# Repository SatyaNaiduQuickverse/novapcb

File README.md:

# novapcb — Nova Flight Controller (FC) PCB

Custom flight controller board for the Nova drone platform. **Status: scoping / greenfield.** No schematics committed yet.

## What this is

A from-scratch FC PCB that drops into the existing Nova drone-Pi software stack. It must remain wire-compatible with the autopilot the system currently uses (a Holybro Pixhawk 6X over USB-CDC MAVLink), because the rest of the stack — ELRS RC link, MAVROS, BLE pre-flight, Hailo vision, phone app — all assumes that contract and is already integrated end-to-end. v1 = functional drop-in, single-PCB on a new tray. v2 = FMUv6X mechanical drop-in.

This is not an attempt to write a new autopilot. The plan is to run an ArduPilot-compatible firmware (or MAVLink-shim equivalent) on a custom board sized and connectorized to fit the Nova frame, with sensors and IO chosen for our specific airframe.

## What this is NOT

- Not the drone-side Pi services. Those live in `~/drone_handoff` (CRSF translator, MAVROS telemetry pump, BLE GATT server) — see `docs/SYSTEM_CONTEXT.md`.
- Not the ground bridge or phone app. Those are `~/novaros` and `~/novaapp_recovery`.
- Not a from-scratch flight stack. The board must speak ArduPilot/MAVLink.

## Repo layout

```
hardware/
  kicad/        # schematic + PCB sources (KiCad 8)
  exports/      # gerbers, drill, pick-and-place — generated, not handwritten
docs/
  SYSTEM_CONTEXT.md       # where the FC sits in the Nova stack
  INTERFACE_CONTRACT.md   # exact pin / protocol contract with the rest of the system
  DECISIONS.md            # locked v1 scoping decisions (MCU, form factor, channels, …)
  OPEN_QUESTIONS.md       # stub for future open questions (post-2026-05-18 lock)
firmware/      # ArduPilot board definition + any board-bringup code
bom/           # parts list, sourcing notes
mechanical/    # mounting holes, stack-up, frame-fit references
```

## Where to start reading

1. `docs/SYSTEM_CONTEXT.md` — the wider Nova stack the FC plugs into.
2. `docs/INTERFACE_CONTRACT.md` — pin-level constraints.
3. `docs/DESIGN_PHASES.md` — canonical execution plan (Phase 0..9 + 0.5/2.5/3.5/6.5).
4. `docs/CONFIDENCE_MAP.md` — subsystem confidence + evidence.
5. `docs/ENGINEERING_RIGOR.md` — non-negotiable commitments.
6. `docs/SIMULATION_PLAN.md` — Phase 6 sim detail.
7. `docs/TASK_CONTRACTS.md` — input/output contracts per sub-phase.
8. `docs/RETROSPECTIVES.md` — hourly self-review framework.
9. `docs/COORDINATION.md` — supervisor + nova-coord setup.
10. `docs/COMMUNICATION.md` — master ↔ worker protocol.
11. `docs/DECISIONS.md` — locked v1 scoping decisions.

## Workflow

PCB work on this project is code-driven where it can be: sources in KiCad, exports automated, BOM diffable. The intent is to keep schematic/layout reviewable in PRs the same way firmware changes are. See `CLAUDE.md` §6 for the full workflow.

## Hardware host

Design and build environment is a Raspberry Pi 5 (16 GB) with a Hailo-8 hat — the same Pi that runs the drone-side stack in dockerized form. KiCad runs natively on the Pi.

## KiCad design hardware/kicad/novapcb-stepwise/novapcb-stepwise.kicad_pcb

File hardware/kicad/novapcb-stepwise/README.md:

# novapcb-stepwise — incremental-integration board (v1.1+)

The single `.kicad_pcb` that grows subsystem by subsystem per
`docs/PLACEMENT_ROUTING_GATES.md` §0 and the integration order in
`docs/SUBSYSTEM_CONTRACTS.md` §4.

## Status

- **Step 1 (C — MCU_CORE):** placed + gates 1/3/4/12 GREEN.
- **Step 2 (E — BARO_I2C):** placed (U4, U7, C51, C52, C71, C72, R11, R12).
- Steps 3-10: future PRs (one per subsystem / integration step).

## How to regenerate

```bash
# Step 1 — place C only
python3 step1_place_C.py
# Step 2 — add E (BARO_I2C) on top of the Step-1 board
python3 step2_place_E.py

# Run the gates (each returns 0 = green, 1 = fail)
python3 gate1_bbox_overlap.py    # bbox-overlap + self-test
python3 gate3_uniqueness.py      # netlist ↔ pcb match
python3 gate4_artifact_trust.py  # grep-the-artifact audit
python3 gate12_thermal_U1.py     # per-subsystem thermal (U1 T_j)

# Gate 2 — 3D render (visual eyeball for master audit)
kicad-cli pcb render --side top    --output render_top.png novapcb-stepwise.kicad_pcb
kicad-cli pcb render --side bottom --output render_bot.png novapcb-stepwise.kicad_pcb
```

## Files

| File | Purpose |
|---|---|
| `novapcb-stepwise.kicad_pcb` | the growing board (committed) |
| `fp-lib-table`               | absolute-path footprint libs (KiCad 9 KIPRJMOD workaround) |
| `step1_place_C.py`           | Step-1 placer: U1, Y1, FB1, 16 caps, 3 resistors |
| `step2_place_E.py`           | Step-2 placer: U4 (DPS310), U7 (BMP388), C51/52/71/72, R11/12 |
| `gate1_bbox_overlap.py`      | Gate 1 verifier (with deliberate-bad self-test) |
| `gate3_uniqueness.py`        | Gate 3: every netlist refdes in .kicad_pcb exactly once |
| `gate4_artifact_trust.py`    | Gate 4: parse the actual .kicad_pcb, don't trust placer's "OK" |
| `gate12_thermal_U1.py`       | Gate 12: U1 worst-case T_j (analytical + Elmer FE attempt) |
| `render_top.png` / `render_bot.png` | Gate 2: 3D renders (visual audit) |

## Step 1 — C (MCU_CORE) placement summary

Per `docs/SUBSYSTEM_CONTRACTS.md §C`:

- **U1** STM32H743VIT6 LQFP-100 at **(45, 35)** mm — geometric center of board.
- **Y1** 8 MHz HSE crystal at W edge, vertically between U1 pins 12 (PH0)
  and 13 (PH1). Rotated 90° so the 3.2 mm dim is in Y.
- **C24, C25** xtal load caps (18 pF) flanking Y1, further W.
- **C11..C15** per-VDD-pin 100 nF decap (5 caps, one per VDD pin: 11 W, 27 S,
  50 S, 75 E, 100 N).
- **C17** (VCAP1, 2.2 µF) S band near pin 48.
- **C18** (VCAP2, 2.2 µF) E band near pin 73.
- **C19, C20, FB1** VDDA chain (100 nF + 1 µF + ferrite) W band near pin 21.
- **C21, C22, R1** VREF+ chain (100 nF + 1 µF + 0R tie) W band near pin 20.
- **C23, R2** VBAT (100 nF + 0R tie to +3V3) W band near pin 6.
- **C26** NRST decap (100 nF) W band near pin 14.
- **R3** BOOT0 pulldown (10k) N band near pin 94.
- **C16** bulk decoupling (4.7 µF 0805) N band, +X-offset from R3.

All 22 C-subsystem footprints + U1 + 4 corner mounting holes are on-board.
The remaining 103 footprints (subsystems A, B, D, E, F, G, H) are PARKED at
X ≥ 110 mm — they will be positioned by future Step-N PRs.

## Sub-phase 1.0 — workflow workaround

KiCad 9's `pcbnew.FootprintLoad` returns `None` for `kinet2pcb`, so we
**clone-and-strip** the v1.1 source `.kicad_pcb` (which has all 125
SKiDL-generated footprints already loaded) via an S-expression rewrite
that drops tracks/vias/zones/Edge.Cuts shapes/original mounting holes.
`pcbnew` then handles repositioning. See `step1_place_C.py:sexp_strip()`.

## Gate-7 note

LQFP-100 (`Package_QFP:LQFP-100_14x14mm_P0.5mm`) is a gull-wing
package — **no exposed thermal pad** — so Gate 7 thermal-vias-under-U1
is N/A. The MCU dissipates ≤500 mW through its 100 leads to the planes
(planes added in the cross-subsystem routing PR).

## Gate-12 note

Two-track T_j evidence per `docs/PLACEMENT_ROUTING_GATES.md` §Gate 13:

- **Analytical (with planes, JESD51-7):** T_j worst = 47.5 °C at P=0.5W,
  T_amb=25°C, Theta_ja=45°C/W (ST DS12110 §6.1). Margin to 105°C
  spec = **57.5 °C**. The cross-subsystem +3V3 + GND planes (added in
  the cross-subsystem routing PR) deliver this regime.
- **Elmer 3D FE (bare FR4, no planes):** T_j ≈ 103 °C. **Marginal**
  (1.8°C from spec) but expected — bare FR4 has no copper spreader,
  so this is a worst-case lower bound for the placement before planes
  land. As soon as the +3V3 / GND planes are present, T_j drops toward
  the analytical 47.5°C.

**3D body-source convention lesson (caught 2026-05-22):** Elmer's
`HeatSolver` expects `Heat Source` in **W/kg** (per unit MASS), not
W/m³. Solver internally multiplies by `Density`. Setting raw W/m³
over-sources by the density factor (~1850× for FR4). Validated against
1D thin-slab analytical to **1.00× match** — see
`sims/validation/VALIDATION_RESULTS.md` §3.

Convergence note: medium→fine mesh delta is 5.63% (just above the <5%
bar). The next iteration of `gate12_thermal_U1.py` should push to a
finer mesh or document why 5.6% is acceptable for a "bare-FR4
upper bound that won't be the ship-state anyway."

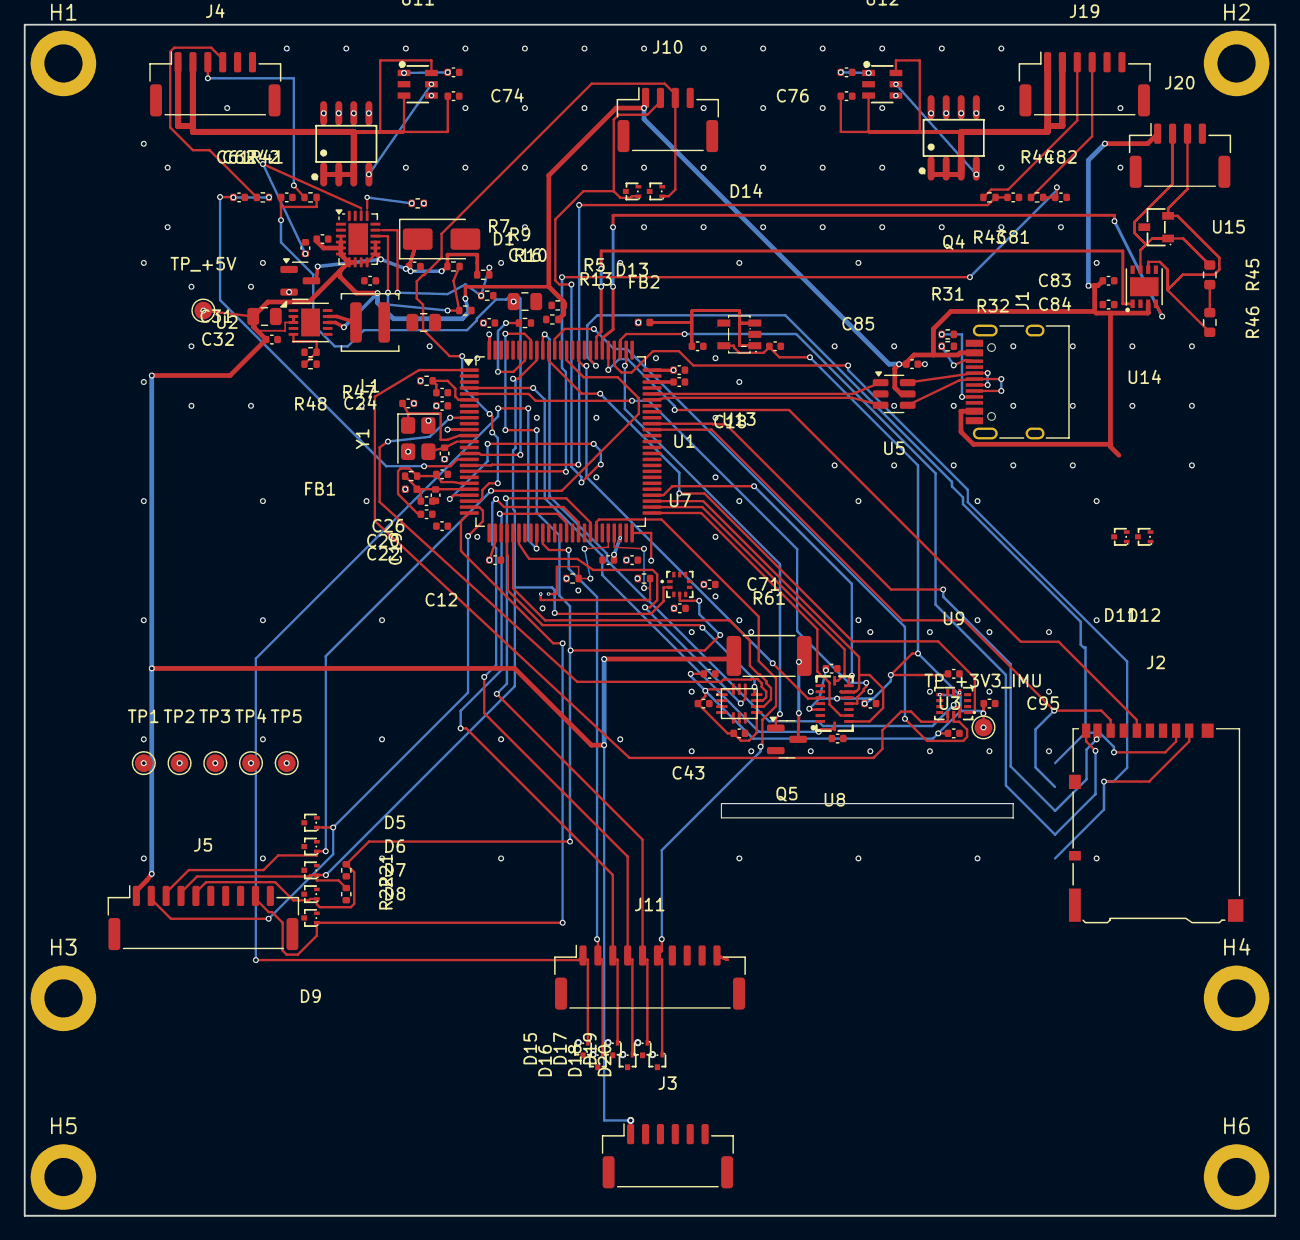
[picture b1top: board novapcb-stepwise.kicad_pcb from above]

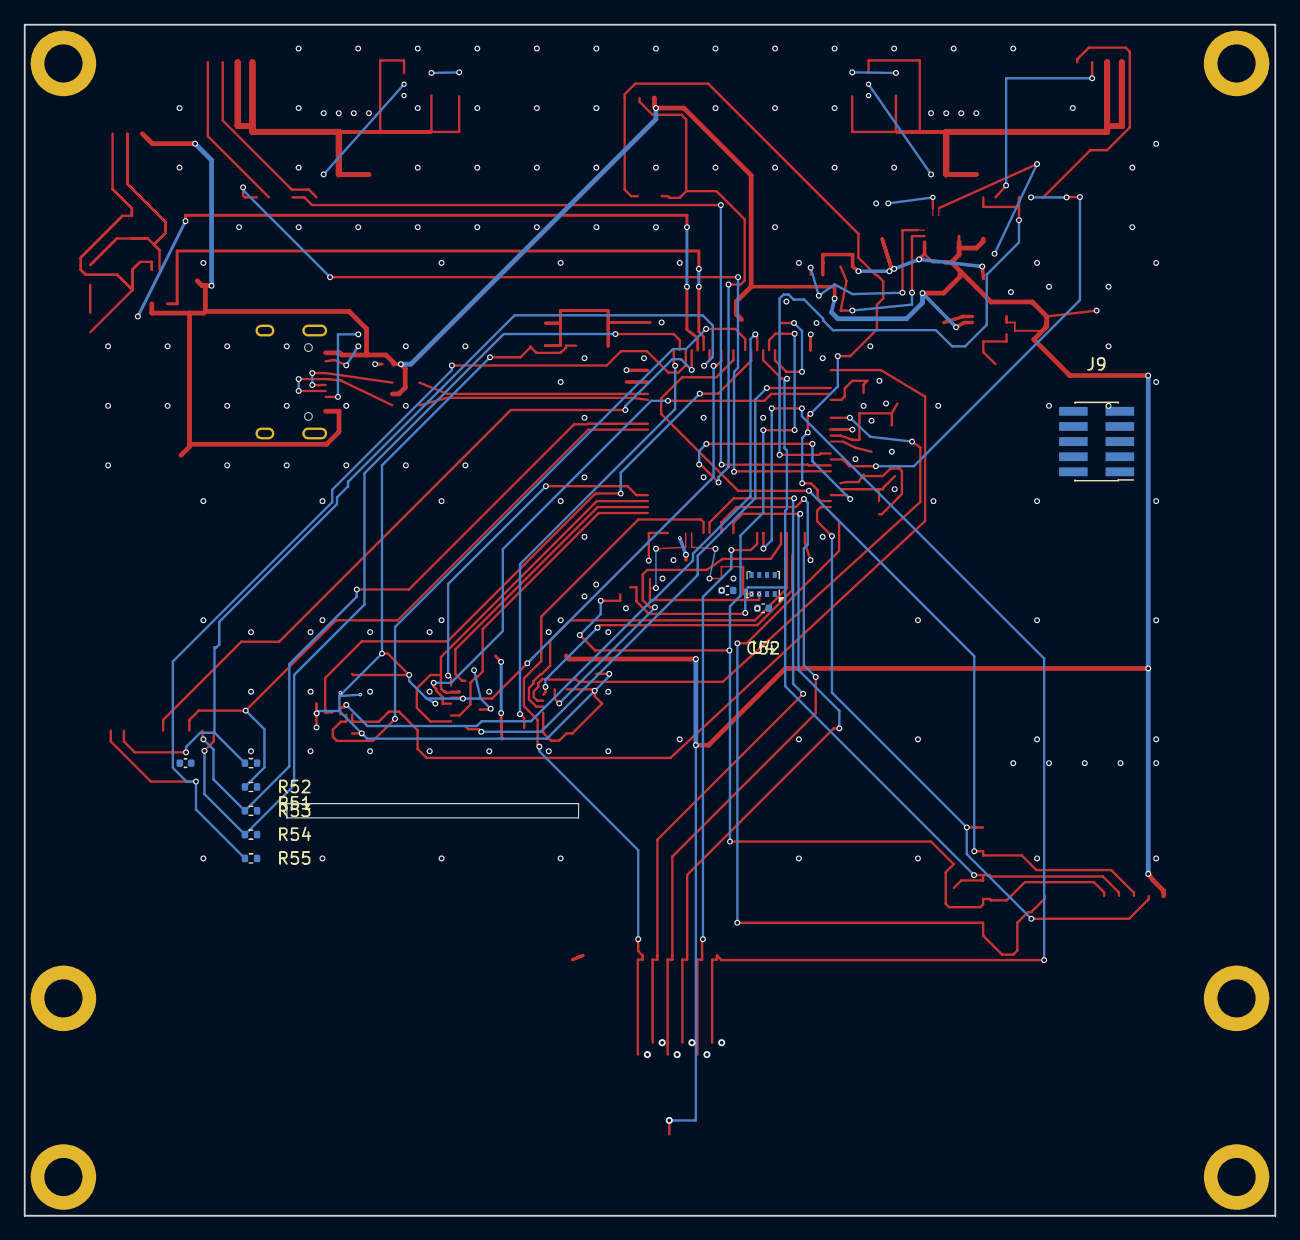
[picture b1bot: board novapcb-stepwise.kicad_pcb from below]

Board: 6 copper layers, 105.0 x 100.0 mm, 141 parts (10 on the bottom side), 94 nets.

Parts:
C7, C8, C11, C12, C13, C14, C15, C19, C21, C23, C26, C32, C34, C41, C42, C51, C52, C61, C62, C63, C71, C72, C74, C76, C81, C82, C83, C84, C85, C91, C92, C94, C95, C96: 100nF; C_0402_1005Metric
C9, C20, C22, C73, C75, C77, C78, C93: 1uF; C_0402_1005Metric
C16: 4.7uF; C_0805_2012Metric
C17, C18, C43: 2.2uF; C_0402_1005Metric
C24, C25: 18pF; C_0402_1005Metric
C31: 10uF; C_0805_2012Metric
C33: 22uF; C_0805_2012Metric
D1: SMAJ6.0A; D_SMA
D5, D6, D7, D8, D9, D11, D12, D13, D14, D15, D16, D17, D18, D19, D20: ESD7L5.0DT5G; SOT-723_L1.2-W0.8-P0.40-LS1.2-BR
FB1, FB2: 600R@100MHz; L_0402_1005Metric
H1, H2, H3, H4, H5, H6: M3
J1: USB-C_2.0; USB_C_Receptacle_HRO_TYPE-C-31-M-12
J2: microSD_DM3AT; microSD_HC_Hirose_DM3AT-SF-PEJM5
J3: TELEM_6P; JST_GH_SM06B-GHS-TB_1x06-1MP_P1.25mm_Horizontal
J4: MAUCH_6P; JST_GH_SM06B-GHS-TB_1x06-1MP_P1.25mm_Horizontal
J5: GPS_MAG_10P; JST_GH_SM10B-GHS-TB_1x10-1MP_P1.25mm_Horizontal
J9: SWD_10P; PinHeader_2x05_P1.27mm_Vertical_SMD
J10: CRSF_4P; JST_GH_SM04B-GHS-TB_1x04-1MP_P1.25mm_Horizontal
J11: ESC_OUT; JST_GH_SM10B-GHS-TB_1x10-1MP_P1.25mm_Horizontal
J19: MAUCH2_6P; JST_GH_SM06B-GHS-TB_1x06-1MP_P1.25mm_Horizontal
J20: CAN_4P; JST_GH_SM04B-GHS-TB_1x04-1MP_P1.25mm_Horizontal
L1: 2.2uH XAL4020; L_Coilcraft_XAL4020-XXX
Q2: AO3401A; SOT-23
Q3, Q4: AO4262E; SOIC-8_L4.9-W3.9-P1.27-LS6.0-BL
Q5: AO3400A; SOT-23
R1, R2: 0R; R_0402_1005Metric
R3, R5, R8, R10, R13: 10k; R_0402_1005Metric
R4: 42.2k; R_0402_1005Metric
R7: 30.1k; R_0402_1005Metric
R9: 51k; R_0402_1005Metric
R11, R12, R21, R22: 4.7k; R_0402_1005Metric
R31, R32: 5.1k; R_0402_1005Metric
R41, R42, R43, R44: 1k; R_0402_1005Metric
R45: 120R; R_0603_1608Metric
R46: 0R; R_0603_1608Metric
R47: 562k; R_0402_1005Metric
R48: 180k; R_0402_1005Metric
R51, R52, R53, R54, R55: 47k; R_0402_1005Metric
R61: TBD_SIM_OUT; R_2512_6332Metric
TP1: +5V_BEC; TestPoint_Pad_D1.5mm
TP2: +3V3; TestPoint_Pad_D1.5mm
TP3: GND_REF; TestPoint_Pad_D1.5mm
TP4: +3V3-2; TestPoint_Pad_D1.5mm
TP5: GND_REF-2; TestPoint_Pad_D1.5mm
TP_+3V3_IMU: +3V3_IMU; TestPoint_Pad_D1.5mm
TP_+5V: +5V; TestPoint_Pad_D1.5mm
U1: STM32H743VITx; LQFP-100_14x14mm_P0.5mm
U2: TPS62177DQC; DFN-10-1EP_3x3mm_P0.5mm_EP1.58x2.35mm
U3: ICM-42688-P_LGA-14_2.5x3mm_P0.5mm
U4: DPS310; Bosch_LGA-8_2x2.5mm_P0.65mm_ClockwisePinNumbering
U5: USBLC6-2P6; SOT-23-6
U6: TPS25940A; QFN-20-1EP_3x4mm_P0.5mm_EP1.65x2.65mm
U7: LPS22HB; HLGA-10L_LPS22HBTR
U8: BMI088; LGA-16_L4.5-W3.0-P0.50-BL
U9: LSM6DSV16X; LGA-14_L3.0-W2.5-P0.50-BR
U11, U12: LM74700-Q1; SOT-23-6_L2.9-W1.6-P0.95-LS2.8-TL
U13: LP5907MFX-3.3; SOT-23-5_L3.0-W1.7-P0.95-LS2.8-BR
U14: TJA1051TK/3; HVSON-8_L3.0-W3.0-P0.65-BL-EP
U15: PESD2CAN; SOT-23-3_L2.9-W1.3-P1.90-LS2.4-BR
Y1: 8MHz; Crystal_SMD_3225-4Pin_3.2x2.5mm

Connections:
+3V3: C11.1, C12.1, C13.1, C14.1, C15.1, C16.1, C33.1, C34.1, C51.1, C52.1, C63.1, C71.1, C72.1, C84.1, FB1.1, FB2.1, J2.4, J5.8, J9.1, L1.2, R2.1, R11.1, R12.1, R21.1, R22.1, R47.1, R51.1, R52.1, R53.1, R54.1, R55.1, TP2.1, TP4.1, U1.11, U1.27, U1.50, U1.75, U1.100, U2.10, U4.2, U4.6, U4.8, U7.1, U7.6, U7.10, U14.5
+3V3A: C19.1, C20.1, FB1.2, R1.1, U1.21
+3V3_IMU: C41.1, C42.1, C43.1, C78.1, C91.1, C92.1, C93.1, C94.1, C95.1, C96.1, TP_+3V3_IMU.1, U3.8, U3.14, U8.3, U8.11, U9.5, U9.8, U13.5
+3V3_IMU_PRE: C77.1, FB2.2, U13.1, U13.3
+5V: C9.1, C31.1, C32.1, C83.1, C85.1, J1.A4, J1.A9, J1.B4, J1.B9, J3.1, J5.1, J10.1, J20.1, R5.2, R13.2, R61.1, TP_+5V.1, U2.2, U2.3, U2.8, U5.5, U6.3, U6.4, U6.5, U6.6, U6.7, U6.8, U14.3
+5V_BEC: Q2.2, Q3.5, Q3.6, Q3.7, Q3.8, Q4.5, Q4.6, Q4.7, Q4.8, TP1.1, U11.4, U12.4
+5V_BEC_A: C74.1, J4.1, J4.2, Q3.1, Q3.2, Q3.3, U11.3, U11.6
+5V_BEC_B: C76.1, J19.1, J19.2, Q4.1, Q4.2, Q4.3, U12.3, U12.6
+5V_BEC_PROT: C8.1, D1.1, Q2.3, R7.1, R9.1, U6.9, U6.10, U6.11, U6.12, U6.13
BATT2_CURRENT_SENS: C82.1, R44.2, U1.18
BATT2_VOLTAGE_SENS: C81.1, R43.2, U1.17
BATT_CURRENT_SENS: C62.1, R42.2, U1.16
BATT_VOLTAGE_SENS: C61.1, R41.2, U1.15
BOOT0: R3.1, U1.94
BUZZER: D9.1, J5.9, U1.25
CAN1_RX: U1.81, U14.4
CAN1_TX: U1.82, U14.1
CANH_NET: J20.2, R45.1, U14.7, U15.1
CANL_NET: J20.3, R46.2, U14.6, U15.2
CAN_TERM_MID: R45.2, R46.1
EFUSE_DVDT: C7.1, U6.18
EFUSE_EN: R7.2, R8.1, U6.14
EFUSE_FLT: R13.1, U6.20
EFUSE_ILIM: R4.1, U6.17
EFUSE_OVP: R9.2, R10.1, U6.15
EFUSE_PGOOD: R5.1, U6.2
GND: C7.2, C8.2, C9.2, C11.2, C12.2, C13.2, C14.2, C15.2, C16.2, C17.2, C18.2, C19.2, C20.2, C21.2, C22.2, C23.2, C24.2, C25.2, C26.2, C31.2, C32.2, C33.2, C34.2, C41.2, C42.2, C43.2, C51.2, C52.2, C61.2, C62.2, C63.2, C71.2, C72.2, C73.2, C74.2, C75.2, C76.2, C77.2, C78.2, C81.2, C82.2, C83.2, C84.2, C85.2, C91.2, C92.2, C93.2, C94.2, C95.2, C96.2, D1.2, D5.2, D6.2, D7.2, D8.2, D9.2, D11.2, D12.2, D13.2, D14.2, D15.2, D16.2, D17.2, D18.2, D19.2, D20.2, H5.1, H6.1, J1.A1, J1.A12, J1.B1, J1.B12, J1.S1, J2.3, J2.6, J3.6, J3.MP, J4.5, J4.6, J5.10, J9.3, J9.5, J9.7, J9.8, J9.9, J10.4, J11.10, J19.5, J19.6, J20.4, Q2.1, Q5.2, R3.2, R4.2, R8.2, R10.2, R31.2, R32.2, R48.2, TP3.1, TP5.1, U1.10, U1.19, U1.26, U1.49, U1.74, U1.99, U2.1, U2.6, U2.11, U3.4, U4.1, U4.5, U4.7, U5.2, U6.1, U6.16, U6.21, U7.3, U7.5, U7.8, U7.9, U8.4, U8.6, U8.7, U9.6, U9.7, U11.2, U12.2, U13.2, U14.2, U14.8, U14.9, U15.3, Y1.2, Y1.4
GPS1_RX: D6.1, J5.3, U1.87
GPS1_TX: D5.1, J5.2, U1.24
HEATER_DRAIN: Q5.3, R61.2
HEATER_PWM: Q5.1, U1.77
HSE_IN: C24.1, U1.12, Y1.1
HSE_OUT: C25.1, U1.13, Y1.3
I2C1_SCL: D7.1, J5.4, R22.2, U1.92, U7.2
I2C1_SDA: D8.1, J5.5, R21.2, U1.93, U7.4
I2C2_SCL: R12.2, U1.46, U4.4
I2C2_SDA: R11.2, U1.47, U4.3
IMU1_CS: U1.9, U3.10
IMU2_ACC_CS: U1.51, U8.14
IMU2_ACC_INT1: U1.4, U8.16
IMU2_GYR_CS: U1.85, U8.5
IMU2_GYR_INT3: U1.5, U8.12
IMU3_CS: U1.1, U9.12
IMU3_INT1: U1.36, U9.4
MAUCH2_CURR_PRE: J19.4, R44.1
MAUCH2_VBAT_PRE: J19.3, R43.1
MAUCH_CURR_PRE: J4.4, R42.1
MAUCH_VBAT_PRE: J4.3, R41.1
MOT1: D15.1, J11.1, U1.34
MOT2: D16.1, J11.2, U1.35
MOT3: D17.1, J11.3, U1.39
MOT4: D18.1, J11.4, U1.41
MOT5: D19.1, J11.5, U1.43
MOT6: D20.1, J11.6, U1.44
MOT7: J11.7, U1.95
MOT8: J11.8, U1.96
NRST: C26.1, J9.10, U1.14
ORING_A_GATE: Q3.4, U11.5
ORING_A_VCAP: C73.1, U11.1
ORING_B_GATE: Q4.4, U12.5
ORING_B_VCAP: C75.1, U12.1
SDMMC1_CLK: J2.5, U1.80
SDMMC1_CMD: J2.2, R51.2, U1.83
SDMMC1_D0: J2.7, R52.2, U1.65
SDMMC1_D1: J2.8, R53.2, U1.66
SDMMC1_D2: J2.9, R54.2, U1.78
SDMMC1_D3: J2.1, R55.2, U1.79
SPI1_MISO: U1.30, U3.9
SPI1_MOSI: U1.31, U3.12
SPI1_SCK: U1.29, U3.11
SPI2_MISO: U1.53, U8.10, U8.15
SPI2_MOSI: U1.54, U8.9
SPI2_SCK: U1.52, U8.8
SPI3_MISO: U1.90, U9.1
SPI3_MOSI: U1.91, U9.14
SPI3_SCK: U1.89, U9.13
SWCLK: J9.4, U1.76
SWDIO: J9.2, U1.72
U2_FB: R47.2, R48.1, U2.5
U2_SW: L1.1, U2.9
UART4_RX: D14.1, J10.3, U1.23
UART4_TX: D13.1, J10.2, U1.22
UART7_RX: D12.1, J3.3, U1.37
UART7_TX: D11.1, J3.2, U1.38
USBC_CC1: J1.A5, R31.1
USBC_CC2: J1.B5, R32.1
USBC_D_M_PRE: J1.A7, J1.B7, U5.4
USBC_D_P_PRE: J1.A6, J1.B6, U5.6
USB_DM: U1.70, U5.3
USB_DP: U1.71, U5.1
VBAT: C23.1, R2.2, U1.6
VCAP1: C17.1, U1.48
VCAP2: C18.1, U1.73
VREF_P: C21.1, C22.1, R1.2, U1.20

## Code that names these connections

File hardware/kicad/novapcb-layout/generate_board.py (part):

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    # (29.5, 17.5) — moved east 1.5mm from initial (28,17.5) so crystal
    # west pads clear MCU east pads (MCU east pad outer X=26.48; crystal
    # pads at X=29.5-1.6=27.9 give 1.42mm gap).
    "Y1":  (28.5, 19.5,    0),   # 4b-θ-final iter3: (28,19.5) put Y1 pad 1 [HSE_IN] at world X=27.7..29.1 overlapping MCU east pads X=24.88..26.48 — no. Moved E 0.5mm. Y1 east pad outer X=30.3 clears J3 MP-S X=30.8 by 0.5mm ✓. Y1 west pad outer X=27.1 clears MCU east X=26.48 by 0.62mm ✓.

    # Crystal load caps (18pF) ADJACENT to Y1, between crystal and MCU body.
    # Load caps further north/south of Y1 to clear Y1's pad bounding box.
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    # ESC pads at 3.0mm pitch (8 pads × 7 gaps = 21mm, X=7.5..28.5)
    # clears H1 keep-out (X<6.25) by 1.25mm on left and H2 keep-out
    # (X>29.75) by 1.25mm on right.
    "J11": ( 7.5,  2.0,    0),   # MOT1 (PB0 TIM3_CH3)
    "J12": (10.5,  2.0,    0),   # MOT2 (PB1 TIM3_CH4)
    "J13": (13.5,  2.0,    0),   # MOT3 (PA0 TIM2_CH1)
    "J14": (16.5,  2.0,    0),   # MOT4 (PA1 TIM2_CH2)
    "J15": (19.5,  2.0,    0),   # MOT5 (PA2 TIM5_CH3)
    "J16": (22.5,  2.0,    0),   # MOT6 (PA3 TIM5_CH4)
    "J17": (25.5,  2.0,    0),   # MOT7 (PD12 TIM4_CH1)
    "J18": (28.5,  2.0,    0),   # MOT8 (PD13 TIM4_CH2)

    # ============ CRSF + USB (3g — top + right edge) ============
    # J1 USB-C at top edge center. PA11 (DM) / PA12 (DP) on STM32 LQFP-100
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
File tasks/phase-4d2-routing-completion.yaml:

id: phase-4d2-routing-completion
phase: "4"
subphase: "4d2"
title: "Phase 4 routing completion — 17 nets, headless net-by-net into the 96%-Freerouted board"
status: in_progress
depends_on:
  - phase-4e-freerouting

inputs:
  files:
    - hardware/kicad/novapcb-layout/novapcb-layout.kicad_pcb
    - hardware/kicad/novapcb-layout/ROUTING_HANDOFF.md
    - hardware/kicad/KICAD9_NOTES.md
  refs:
    - "ROUTING_HANDOFF.md — 17 nets with pad endpoints + per-net hints (USB_DP impedance, SDMMC F.Cu→B.Cu via cluster, etc.)"
    - "KICAD9_NOTES.md API-measure-pad-extents discipline — pad.GetSize() + pad.GetPosition() direct reads; NO estimation"
    - "Phase 4d Rule-13 adjudication — the FAILED scripted whole-board approach (3 iter / 53→81→6 violations); 4d2 is NET-BY-NET into the Freerouted 96%, fundamentally different problem"
    - "Phase 4e Freerouting result — 771 tracks + 153 vias placed; 17 nets have ratlines (some partially-routed by Freerouting, none with locked flag set)"
    - "Net classes (.kicad_pro net_settings) — USB_diffpair W=0.25/S=0.10/diff_gap=0.10, IMU_SPI, SDMMC, DShot, Power_*, Default 0.15mm"

# Falsifiable pre-prediction — per Rule-13-with-options + commit-prediction-before-verification
prediction:
  worker_pre_run_prediction: |
    API-measured pad inventory (per ROUTING_HANDOFF.md):
      Simple F.Cu↔F.Cu shorts (high confidence clean route):
        HSE_OUT       — Y1↔U1↔C25 (all F.Cu, dense MCU east area)
        USART1_RX     — U1.69 (25.68,16) → J3.3 (35.35,22.38) — F.Cu east edge, short hop
        MOT1, MOT2    — U1.34/35 N pins to J11/J12 south edge, parallel routes
        MOT3          — U1.22 W pin to J13 south — longer N-S through dense MCU south area
      Cross-layer F.Cu↔B.Cu (moderate confidence):
        I2C2_SDA/SCL  — F.Cu pullup R11/R12 + MCU pin to B.Cu U4 baro — short F.Cu + 1 via each
        SWDIO/SWCLK   — F.Cu MCU east pins to B.Cu J9 — 1 via each
        NRST          — F.Cu C26 + U1.14 to B.Cu J9.10 — extension of existing route
      Critical-impedance (controlled geometry, moderate confidence):
        USB_DP        — U5.6 (11.64,30.05) → U1.71 (25.68,15) on F.Cu. ~17mm path through
                        dense MCU west area. 90Ω diff pair geometry W=0.25/S=0.10 alongside
                        already-routed USB_DM. Headless length-matching is non-trivial.
      Hardest (moderate-low confidence):
        SDMMC family (6 nets) — F.Cu MCU south (Y=11.32) + east (Y=17.5-18) to B.Cu J2 (Y=1.27),
                                with pullup branches to R51-R55 on B.Cu. All 6 traverse the
                                densest Y=1-11 channel; B.Cu via cluster.

    Predict 11-14 of 17 clear with one-honest-attempt + lock rule. Likely residual:
    SDMMC subset (1-3 nets) + USB_DP (length-match constraint headless-hard).

    DRC: 0 errors on each successfully-routed net. Residual nets stay as ratlines for
    GUI completion or design respin — bounded NAMED list, not a blob.

decision_forks_watched:
  routing-approach:
    fork: "Per-net headless via pcbnew Python API + locked existing Freerouting tracks treated as obstacles"
    expected_classes: [all-17-clear, partial-bounded-residual, broad-failure]
    pre_recommendation: "Try one-honest-attempt per net; lock immediately on success; named-net residual list if any. PARTIAL is the expected outcome and a valid Phase 4d2 result; broad-failure (>8 residual) would escalate."
    actual_resolution: "broad-failure — 0 of 17 cleanly routed; 345 DRC violations introduced by naive L-shape Manhattan with zero obstacle awareness; same root cause as Phase 4d. RULE-13 STOP. Board reverted to pre-4d2 state (771 tracks + 153 vias Freerouting baseline; 0 DRC violations). Hand back to ROUTING_HANDOFF.md GUI flow."
    resolved_via: "Phase 4d2 run + DRC measurement; results in hardware/kicad/novapcb-layout/phase-4d2-results.md"

escalation_log:
  - timestamp: "2026-05-20"
    sub: "4d2 routing approach"
    finding: "Naive L-shape Manhattan router with no obstacle awareness fails uniformly across all 17 nets (28-44 violations per net, primarily tracks_crossing + shorting_items). Same root cause as Phase 4d's 3-iter tripwire (53→81→6 violations). The 96%-Freerouted board has tracks/vias/planes occupying nearly every direct path between MCU pins and the 17 ratline endpoints; line-of-sight L-shapes guaranteed to cross obstacles."
    resolution: "RULE-13 STOP. Per master's 'one honest attempt per net' + 'don't zigzag' directives: one attempt made, all 17 failed for the same reason, did not zigzag or implement obstacle-aware router (out of 'one honest attempt' scope). Reverted board file via git-checkout; verified 0 DRC violations + 771+153 Freerouting baseline. Captured the failed attempt + reasoning in phase-4d2-results.md as a documented dead-end. Recommendation: ROUTING_HANDOFF.md GUI flow (the original Phase 4d adjudication) — KiCad 9 GUI's push-and-shove router has the obstacle-awareness this scripted approach lacks."
    evidence_path: "hardware/kicad/novapcb-layout/phase-4d2-results.md"

outputs:
  files_created:
    - tasks/phase-4d2-routing-completion.yaml
    - hardware/kicad/novapcb-layout/run_route_17nets.py
    - hardware/kicad/novapcb-layout/phase-4d2-results.md
  files_modified:
    - hardware/kicad/novapcb-layout/novapcb-layout.kicad_pcb   # routed nets locked
    - docs/DESIGN_PHASES.md
  pr:
    title: "Phase 4d2: 17-net routing completion (net-by-net headless)"
    branch: hw/phase-4d2-routing-completion-2026-05-20

pass_criteria:
  - "4d2.1: API-measured pad positions for all 17 nets (no estimates). Per-net pad inventory committed to task contract or run script."
  - "4d2.2: One honest attempt per net — no zigzagging (per-net rev-count tripwire). Existing 96%-Freerouted tracks treated as fixed obstacles."
  - "4d2.3: Per routed net: add tracks (+ vias if cross-layer), set IsLocked()=True on my new tracks, run kicad-cli pcb drc, confirm 0 NEW violations."
  - "4d2.4: Honest report — named list of which nets routed cleanly + which remain. Residual is a bounded SPECIFIC named list, not a blob."
  - "4d2.5: kicad-cli pcb drc on the final board — 0 errors required for routed nets; unconnected_items warnings on residual nets are EXPECTED + reported."
  - "4d2.6: If 100% routed: Phase 4f (run_gerber_export.py) is now reachable on the routed board. If residual: it's the bounded named list for human-GUI or design respin."
  - "4d2.7: SOTA self-audit. Actual-vs-predicted reported. Per master's standing: SDMMC + USB_DP are the named risky nets; partial-result is a valid Phase 4d2 outcome, NOT a failure."

estimated_context_kb: 55
estimated_wallclock: "1-3 hours"

notes: |
  Master 4d-decision rationale (paraphrased): scripted whole-board routing has
  been proven infeasible on this dense board (Phase 4d 3-iter tripwire). 4d2 is
  fundamentally different: 96% locked + 17 net-by-net into the gaps. The 4d
  failure mode (router can't find any solution because the WHOLE board is the
  problem) is gone — now the router has to solve per-net "from A to B avoiding
  obstacles" 17 separate times.

  Per master: ONE honest attempt per net. If a net genuinely can't route into
  the available space, leave it + log it + move on. Per-net rev-count tripwire
  prevents zigzag work. Partial result is a fine, honest outcome.

  Don't pre-claim success — report measured outcomes. Residual is the bounded
  named list, not a blob.

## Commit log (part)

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2026-05-24 docs: STATUS.md — T3 3a paused; AWAITING SAI for strategy call
2026-05-25 docs: STATUS.md - 6-PR worker session sign-off; awaiting fresh context for T3 partial
2026-05-26 docs: STATUS.md - 7-PR session sign-off (PR #105 IMU decap review merged); LSM6DSV16X datasheet awaiting Sai
2026-05-26 docs: STATUS.md - PR #106 DRU cleanup merged; Rule 21 codified; worker self-dispatched T3 survey
2026-05-26 docs: STATUS.md - FLIGHT-CRITICAL: T3 partial MOT3-6 routed (PR #107); 6/8 motors functional in v1
2026-05-26 docs: STATUS.md — CORRECT 6/8 to actual 4/8 (MOT1/2 unrouted); task #55 to close gap
2026-05-26 docs: STATUS.md - 6/8 motors ACTUALLY routed (PR #110); Sim 3 SDMMC SI PASS (PR #111)
2026-05-26 docs: STATUS.md - Sim suite COMPLETE (all 4 PASS); Sim 5 PDN remains deferred
2026-05-26 docs: Phase 7a checklist — BOM 9 LCSC TBD + R61 value (post PR #115 regen)
2026-05-26 docs: STATUS.md - 13-PR session sign-off; remaining items Sai-gated
2026-05-26 docs: Phase 7a checklist — add ArduPilot build verify gate (caught dead OSD remnants)
2026-05-30 scratch: freeze-head renders for HTML view
    Generated at freeze head dc1f1a6 via kicad-cli pcb render + export svg:
    - 3d_top.png (264KB, 2000x2000)
    - 3d_bot.png (143KB, 2000x2000)
    - top.svg / bot.svg (F.Cu / B.Cu)
    - In1_Cu.svg / In2_Cu.svg / In3_Cu.svg / In4_Cu.svg (inner planes)
    For HTML preview of final board layout. Scratch branch — not for merge.
2026-05-30 scratch: re-render 3D with --quality high
    Re-render attempt per master 2026-05-30 to surface 3D component bodies.
    DIAGNOSIS (engineering-honest):
    - /usr/share/kicad/3dmodels/ does NOT exist on this build host
    (novatics64 Pi). kicad-packages3d apt package available but NOT
    installed (kicad / kicad-libraries / kicad-footprints / kicad-symbols
    / kicad-templates / kicad-demos all installed; kicad-packages3d is the

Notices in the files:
parts and their libraries:
Cross-verified geometry against community footprints Gripsou/effective-coffee-spoon CC-BY-SA-4.0 and Aerokitties/Kitties-Hardware unlicensed and tetra-aero/ICM-42688-P_breakout GPL-3.0 reference only.
